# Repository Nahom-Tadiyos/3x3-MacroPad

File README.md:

# FrogPad 🐸

The FrogPad is a 3x3 macropad designed for simple desk use. It functions as a customizable shortcut controller, allowing quick access to keybinds and media controls.

The macropad is powered by a Seeed XIAO RP2040 and includes a rotary encoder for volume control, making it a versatile addition to any setup. Its small form factor keeps it unobtrusive while still providing useful functionality.

I designed this project for personal use to improve my productivity and reduce repetitive keyboard actions. The green color and frog theme were chosen simply because I like frogs and wanted something unique on my desk.

## Features:

This design comes with an EC11 Rotary encoder for volume control, and 9 keyswitches with customization available. Powered by Seeed XIAO RP2040, this device will handle any shortcut or command like a pro.

##  How to Use

1. Plug the FrogPad into your computer using a USB-C cable  
2. Flash the firmware onto the Seeed XIAO RP2040  
3. Customize keybinds and macros using KMK firmware on any text editor
4. Use the macropad to trigger shortcuts, macros, or media controls  
5. Rotate the encoder to adjust volume

##  Project Files
This repository includes:
- PCB design files 
- Gerber files for manufacturing
- CAD files
- Firmware source code in python

## Full Assembly in Cad:

## PCB:

## Schematics:

## BOM:

| Component | Quantity | Description | Link |
|----------|--------|-------------|------|
| Seeed XIAO RP2040 | 1 | Microcontroller board | https://www.seeedstudio.com/XIAO-RP2040-p-5026.html |
| Custom PCB | 1 | 3x3 macropad PCB | Gerber files in repo |
| Cherry MX Switches | 9 | Mechanical key switches | https://www.amazon.com/dp/B0CBS25YJ1 |
| DSA Keycaps (Blank) | 9 | Keycaps for switches | https://www.amazon.com/dp/B0BWDTBF1L |
| EC11 Rotary Encoder | 1 | Rotary encoder for volume control | https://www.aliexpress.us/w/wholesale-ec11-rotary-encoder.html |
| M4 x 16mm Screws | 4 | Mounting hardware | https://www.mcmaster.com |

## Future Improvements

- Add RGB lighting
- Bluetooth support
- OLED display to display info

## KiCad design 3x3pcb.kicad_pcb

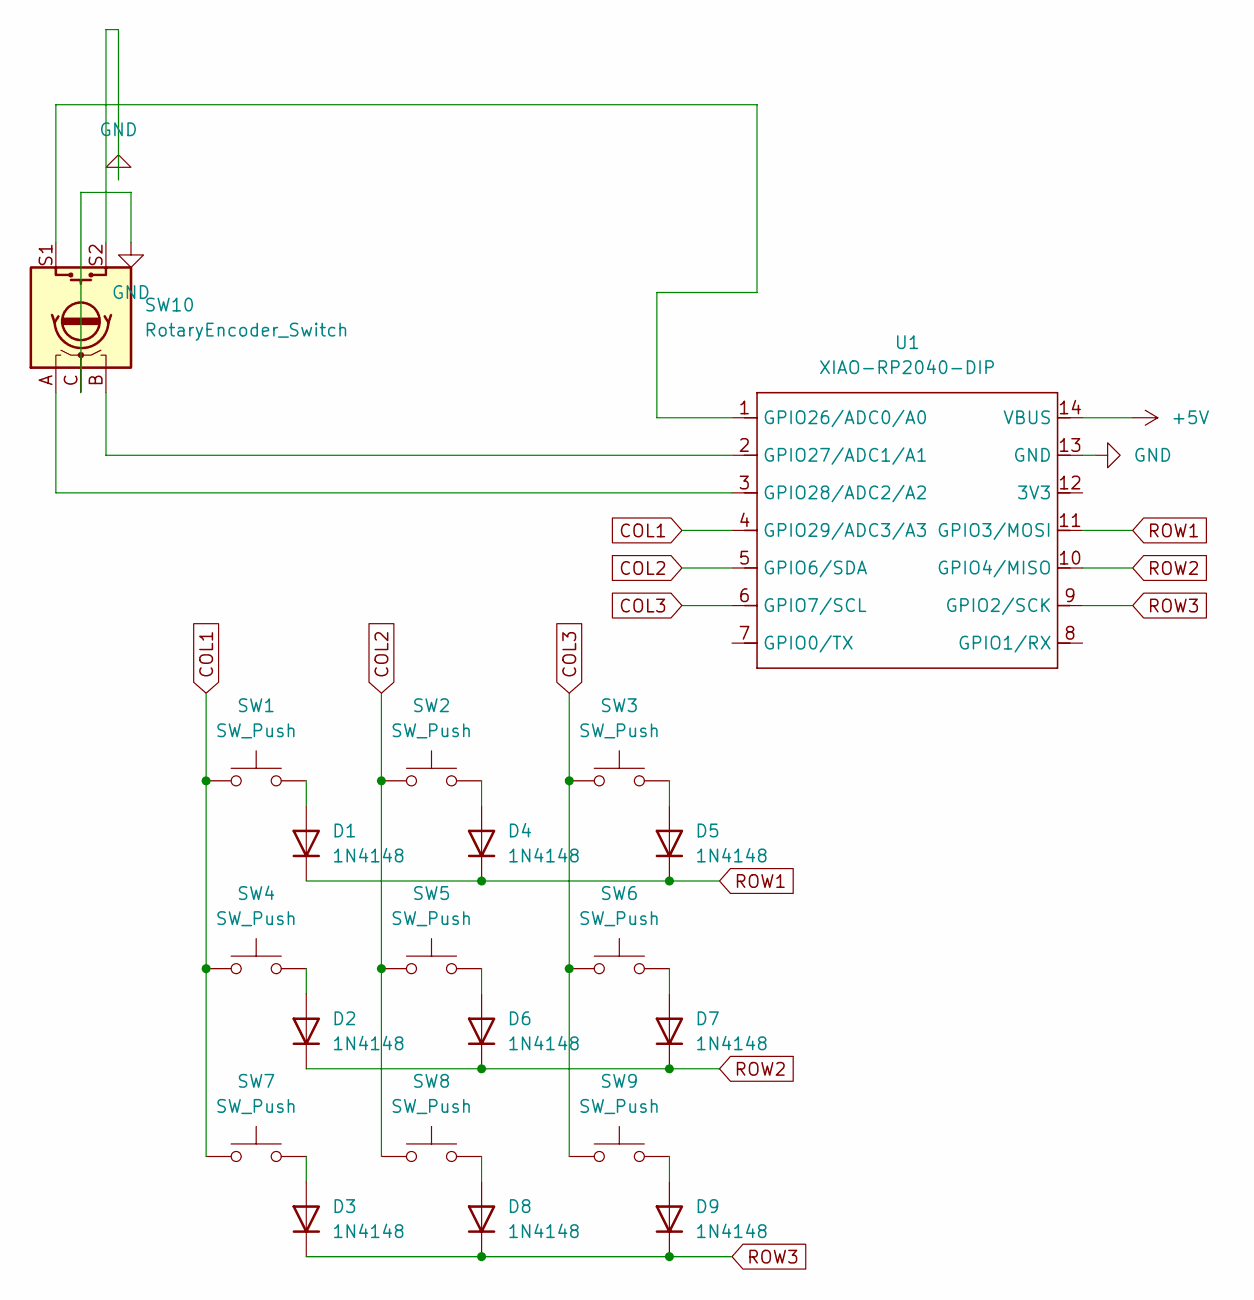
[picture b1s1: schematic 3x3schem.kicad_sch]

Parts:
D1, D2, D3, D4, D5, D6, D7, D8, D9: 1N4148; D_DO-35_SOD27_P7.62mm_Horizontal
SW1, SW2, SW3, SW4, SW5, SW6, SW7, SW8, SW9: SW_Push; SW_Cherry_MX_1.00u_PCB
SW10: RotaryEncoder_Switch; RotaryEncoder_Alps_EC11E-Switch_Vertical_H20mm_CircularMoun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
U1: XIAO-RP2040-DIP

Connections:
+5V: U1.14 (VBUS)
COL1: SW1.1, SW4.1, SW7.1, U1.4 (GPIO29/ADC3/A3)
COL2: SW2.1, SW5.1, SW8.1, U1.5 (GPIO6/SDA)
COL3: SW3.1, SW6.1, SW9.1, U1.6 (GPIO7/SCL)
GND: SW10.C, SW10.S2, U1.13 (GND)
unnamed: D1.2 (A), SW1.2
unnamed: D2.2 (A), SW4.2
unnamed: D3.2 (A), SW7.2
unnamed: D4.2 (A), SW2.2
unnamed: D5.2 (A), SW3.2
unnamed: D6.2 (A), SW5.2
unnamed: D7.2 (A), SW6.2
unnamed: D8.2 (A), SW8.2
unnamed: D9.2 (A), SW9.2
unnamed: SW10.S1, U1.1 (GPIO26/ADC0/A0)
unnamed: SW10.B, U1.2 (GPIO27/ADC1/A1)
unnamed: SW10.A, U1.3 (GPIO28/ADC2/A2)
ROW1: D1.1 (K), D4.1 (K), D5.1 (K), U1.11 (GPIO3/MOSI)
ROW2: D2.1 (K), D6.1 (K), D7.1 (K), U1.10 (GPIO4/MISO)
ROW3: D3.1 (K), D8.1 (K), D9.1 (K), U1.9 (GPIO2/SCK)

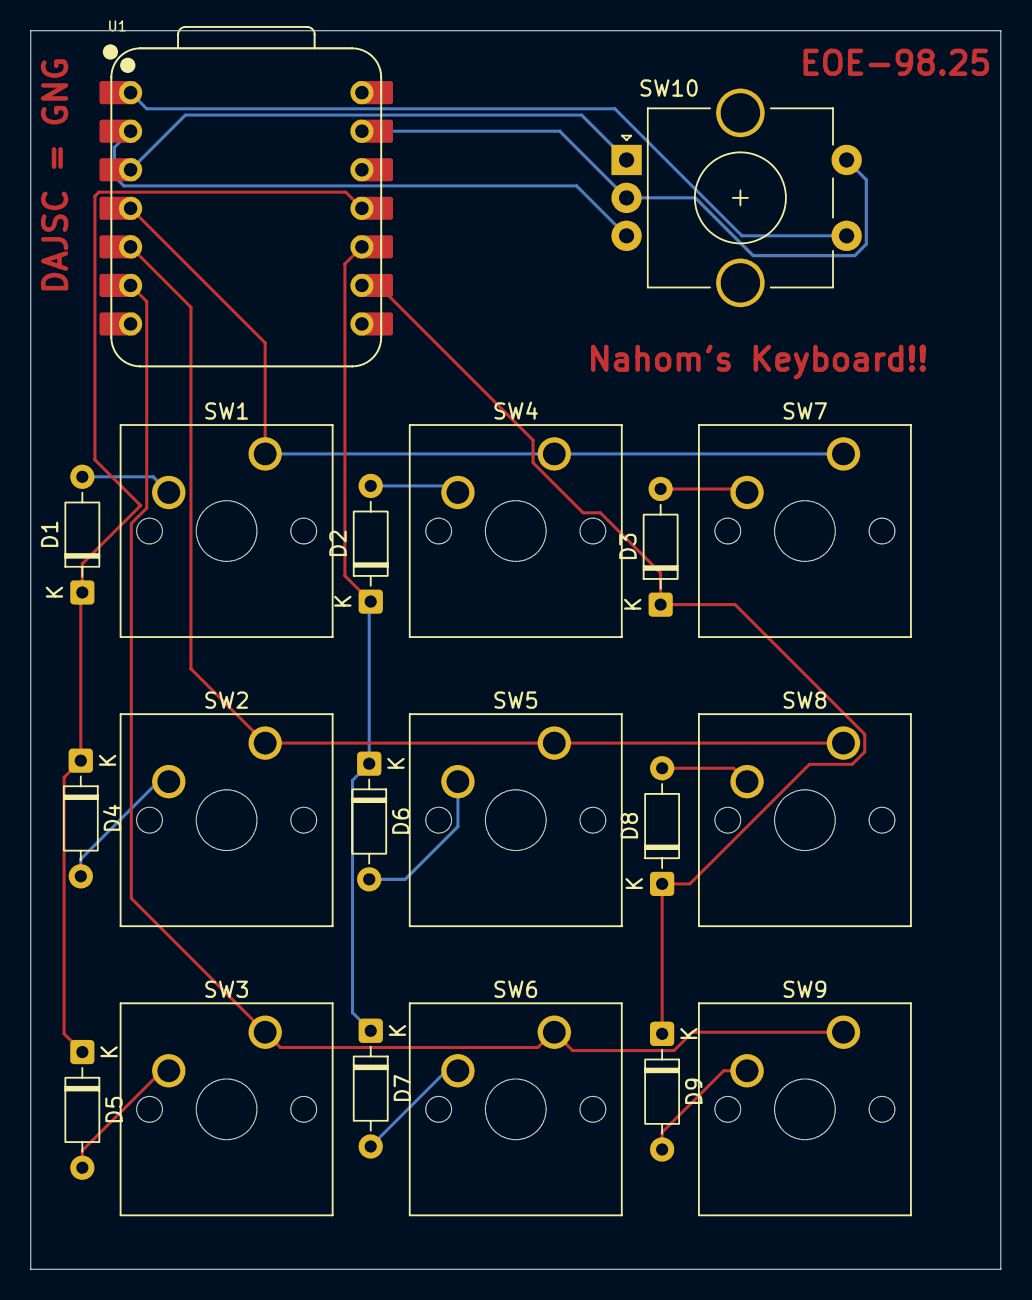
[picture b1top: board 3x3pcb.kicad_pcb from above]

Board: 2 copper layers, 63.9 x 81.6 mm, 20 parts (0 on the bottom side), 19 nets.

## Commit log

2026-03-16 uploading files
    have not organized yet
2026-03-16 Create
2026-03-16 Uploaded Firmware and Production folders
2026-03-16 uploaded my starting readme
2026-03-16 Added PCB Folder
2026-03-16 Added CAD Folder
2026-03-16 Replace dummy images with real screenshots
    Updated placeholder images with actual screenshots.
2026-03-19 Added f3z file as requested
2026-03-19 Revise README for FrogPad project details
    Updated the README to enhance project description and features.
2026-03-19 Add BOM.csv with components and quantities
